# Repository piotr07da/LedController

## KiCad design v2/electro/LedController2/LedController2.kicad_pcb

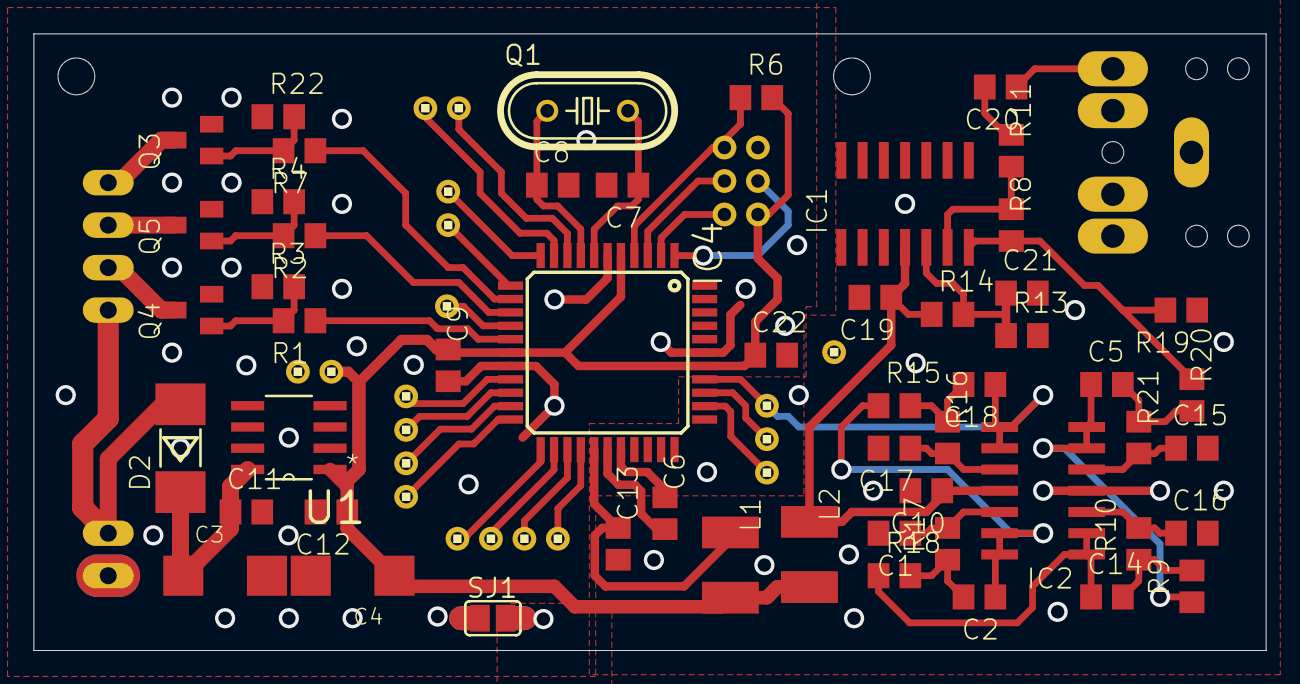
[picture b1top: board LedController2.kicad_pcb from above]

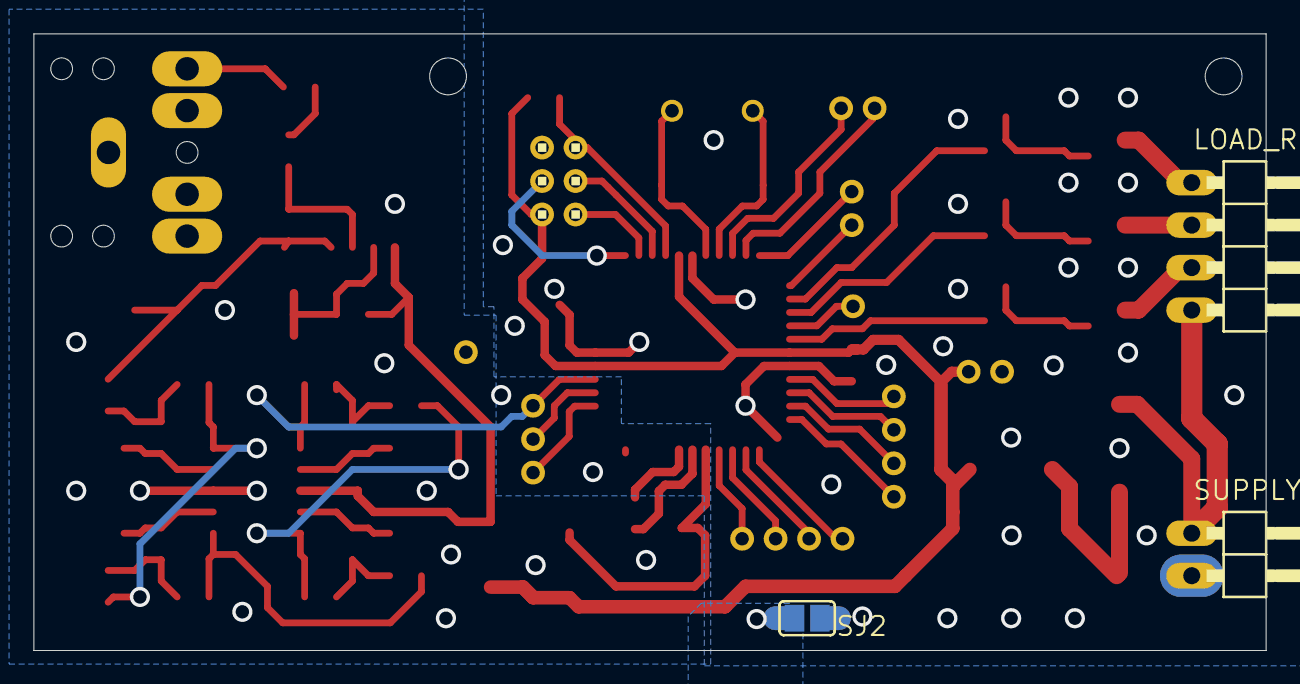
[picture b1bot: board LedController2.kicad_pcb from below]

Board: 2 copper layers, 73.6 x 36.9 mm, 69 parts (4 on the bottom side), 55 nets.

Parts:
@HOLE0, @HOLE1: (no value)
AUDIO: 1X3
AUDIO_GND: 1X1
C1, C15, C16, C17: 2.2n; C0805
C2: 0.47u; C0805
C3, C4: 10u; SMC_C
C5: 10n; C0805
C6, C9, C10, C11, C12, C13, C14, C19, C22: 100n; C0805
C7, C8: 15p; C0805
C18: 4.7u; C0805
C20, C21: 10u; C0805
D2: SM4004; MELF-MLL41
IC1, IC2: LM324D; SO14
IC4: MEGA32-A; TQFP44
INNER_SUPPLY: 1X2
L1, L2: 10u; L1812
LOAD_RGB: 1X04_90
Q1: 14.7456M-HC49-S; HC49_S
Q3, Q4, Q5: IRLML6344; SOT23
R1, R2, R7: 0; R0805
R3, R4, R22: 28k; R0805
R6, R11: 10k; R0805
R8, R13, R14: 100k; R0805
R9: 2.74k; R0805
R10, R19: 6.49k; R0805
R15: 301; R0805
R16: 412; R0805
R17: 1.91k; R0805
R18: 909; R0805
R20: 26.1k; R0805
R21: 43.2k; R0805
SERIAL, SERIAL1: 1X2
SJ1, SJ2: SJ
SUPPLY: 1X02_90
U1: L78L05ABD; SOIC127P600X175-8N
U$1, U$2: 1X4
U$4: 1X1
U$5: 2X3
U$6: JACK35

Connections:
+5V: C4.+, C9.1, C12.1, C22.1, IC4.5, IC4.17, IC4.38, INNER_SUPPLY.1, L1.2, L2.2, R6.2, U1.1, U$5.2
ADC0: AUDIO.1, C18.1, IC2.8, IC2.9, IC4.37
ADC1: AUDIO.2, IC4.36
ADC2: AUDIO.3, IC4.35
AGND: AUDIO_GND.1, C1.2, C6.2, C10.2, C13.2, C15.2, C16.2, C17.2, C19.2, C21.2, IC1.11, IC2.4, IC4.28, R13.2, R19.1, SJ1.2, SJ2.2, U$6.SHUNT_TERMINAL_A_5, U$6.SHUNT_TERMINAL_B_4, U$6.SLEEVE_3
AREF: C6.1, IC4.29
AVCC: C13.1, IC4.27, L1.1
B-: LOAD_RGB.2, Q5.3
G-: LOAD_RGB.3, Q4.3
GND: C3.-, C4.-, C7.2, C8.2, C9.2, C11.2, C12.2, C22.2, IC4.6, IC4.18, IC4.39, INNER_SUPPLY.2, Q3.2, Q4.2, Q5.2, R3.1, R4.1, R22.1, SJ1.1, SJ2.1, SUPPLY.2, U1.2, U1.3, U1.6, U1.7, U$5.6
unnamed: C20.2, R11.1
unnamed: Q3.1, R7.2, R22.2
unnamed: IC4.3, U$5.3
unnamed: IC4.2, U$5.1
unnamed: Q4.1, R1.2, R3.2
unnamed: C3.+, C11.1, D2.C, U1.8
unnamed: IC1.7, R8.2, R19.2, R20.1
unnamed: C14.2, R9.2, R10.1
unnamed: Q5.1, R2.2, R4.2
unnamed: IC4.1, U$5.4
unnamed: IC1.6, R8.1, R11.2
unnamed: C5.1, IC2.6, IC2.7, R9.1
unnamed: C10.1, C19.1, IC1.4, IC2.11, L2.1, R14.1
unnamed: C21.1, IC1.5, R13.1, R14.2
unnamed: C15.1, IC2.5, R21.2
unnamed: C16.1, IC2.3, R10.2
unnamed: C17.1, IC2.10, R16.2
unnamed: C2.1, IC2.13, IC2.14, R15.1
unnamed: C5.2, R20.2, R21.1
unnamed: C18.2, R15.2, R16.1
unnamed: C14.1, IC2.1, IC2.2, R18.1
unnamed: C1.1, IC2.12, R17.2
unnamed: C2.2, R17.1, R18.2
unnamed: C20.1, U$6.TIP_7
unnamed: IC4.22, U$1.4
unnamed: IC4.21, U$1.3
unnamed: IC4.20, U$1.2
unnamed: IC4.19, U$1.1
unnamed: IC4.23, U$2.4
unnamed: IC4.24, U$2.3
unnamed: IC4.25, U$2.2
unnamed: IC4.26, U$2.1
unnamed: IC4.15, U$4.1
PD2: IC4.11, SERIAL1.2
PD3: IC4.12, SERIAL1.1
PWM_LED_B: IC4.14, R2.1
PWM_LED_G: IC4.16, R1.1
PWM_LED_R: IC4.13, R7.1
R-: LOAD_RGB.1, Q3.3
RESET: IC4.4, R6.1, U$5.5
RXD: IC4.9, SERIAL.1
TXD: IC4.10, SERIAL.2
VCC_IN: D2.A, LOAD_RGB.4, SUPPLY.1
XTAL1: C8.1, IC4.8, Q1.1
XTAL2: C7.1, IC4.7, Q1.2

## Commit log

2017-12-31 init
2018-04-20 LedController3 - Particle Photon - schemat i płytka skończone, wygenerowane pliki gerber - wysłane do produkcji do JLCPCB; oraz zalążek kodu na Photon'a
2018-04-22 działający ColorTimeLine, działające wysterowanie PWM, prawidłowe przejścia kolorów
2018-04-23 uzupełnione implementacje w klasie ColorTimeLine potrzebne do zarządzania time linem z aplikacji klienckiej + mały refactor
2018-04-26 porządki
2018-04-29 przerobienie ColorTimePoint.Time z uint8_t na float. Time progress także jako float. Aplikacja kliencka - skończone wyświetlanie - do zrobienia obsługa touch + komunikacja + slidery RGB i progress
2018-04-29 suwak czasu i suwaki sliderów - działające - kominikujące wywołujące i odbierające dane z fake communicatora
2018-05-06 Wersja zaawansowana - klient + photon. Działająca komunikacja z Desktop i Mobile(Android). Fajnie działające suwaki.
2018-05-09 Klient - silniczek komponentów
2018-05-09 color picker - dwie implementacje
2018-05-10 dalsze prace nad HV color pickerem
2018-05-12 doprowadzamy kolor do ładu - potrzeba poprawienia generowania gradient circle po przerobieniu na rysowanie przy pomocy DrawVertices
2018-05-12 no i gradient circle działa, szkoda tylko, że antyaliasing nie działa dla metody DrawVertices
2018-05-13 walka z tcp communicatorem + kolejne poprawki do interpolacji kolorów + kolejne zmiany w hsv color pickerze
2018-05-15 działający HSV color picker + poprawa wydajności - zrobienie mini sliniczka odpalającego z zadanym frame rate'em InvalidateSurface
2022-01-20 LedController2 - kicad
